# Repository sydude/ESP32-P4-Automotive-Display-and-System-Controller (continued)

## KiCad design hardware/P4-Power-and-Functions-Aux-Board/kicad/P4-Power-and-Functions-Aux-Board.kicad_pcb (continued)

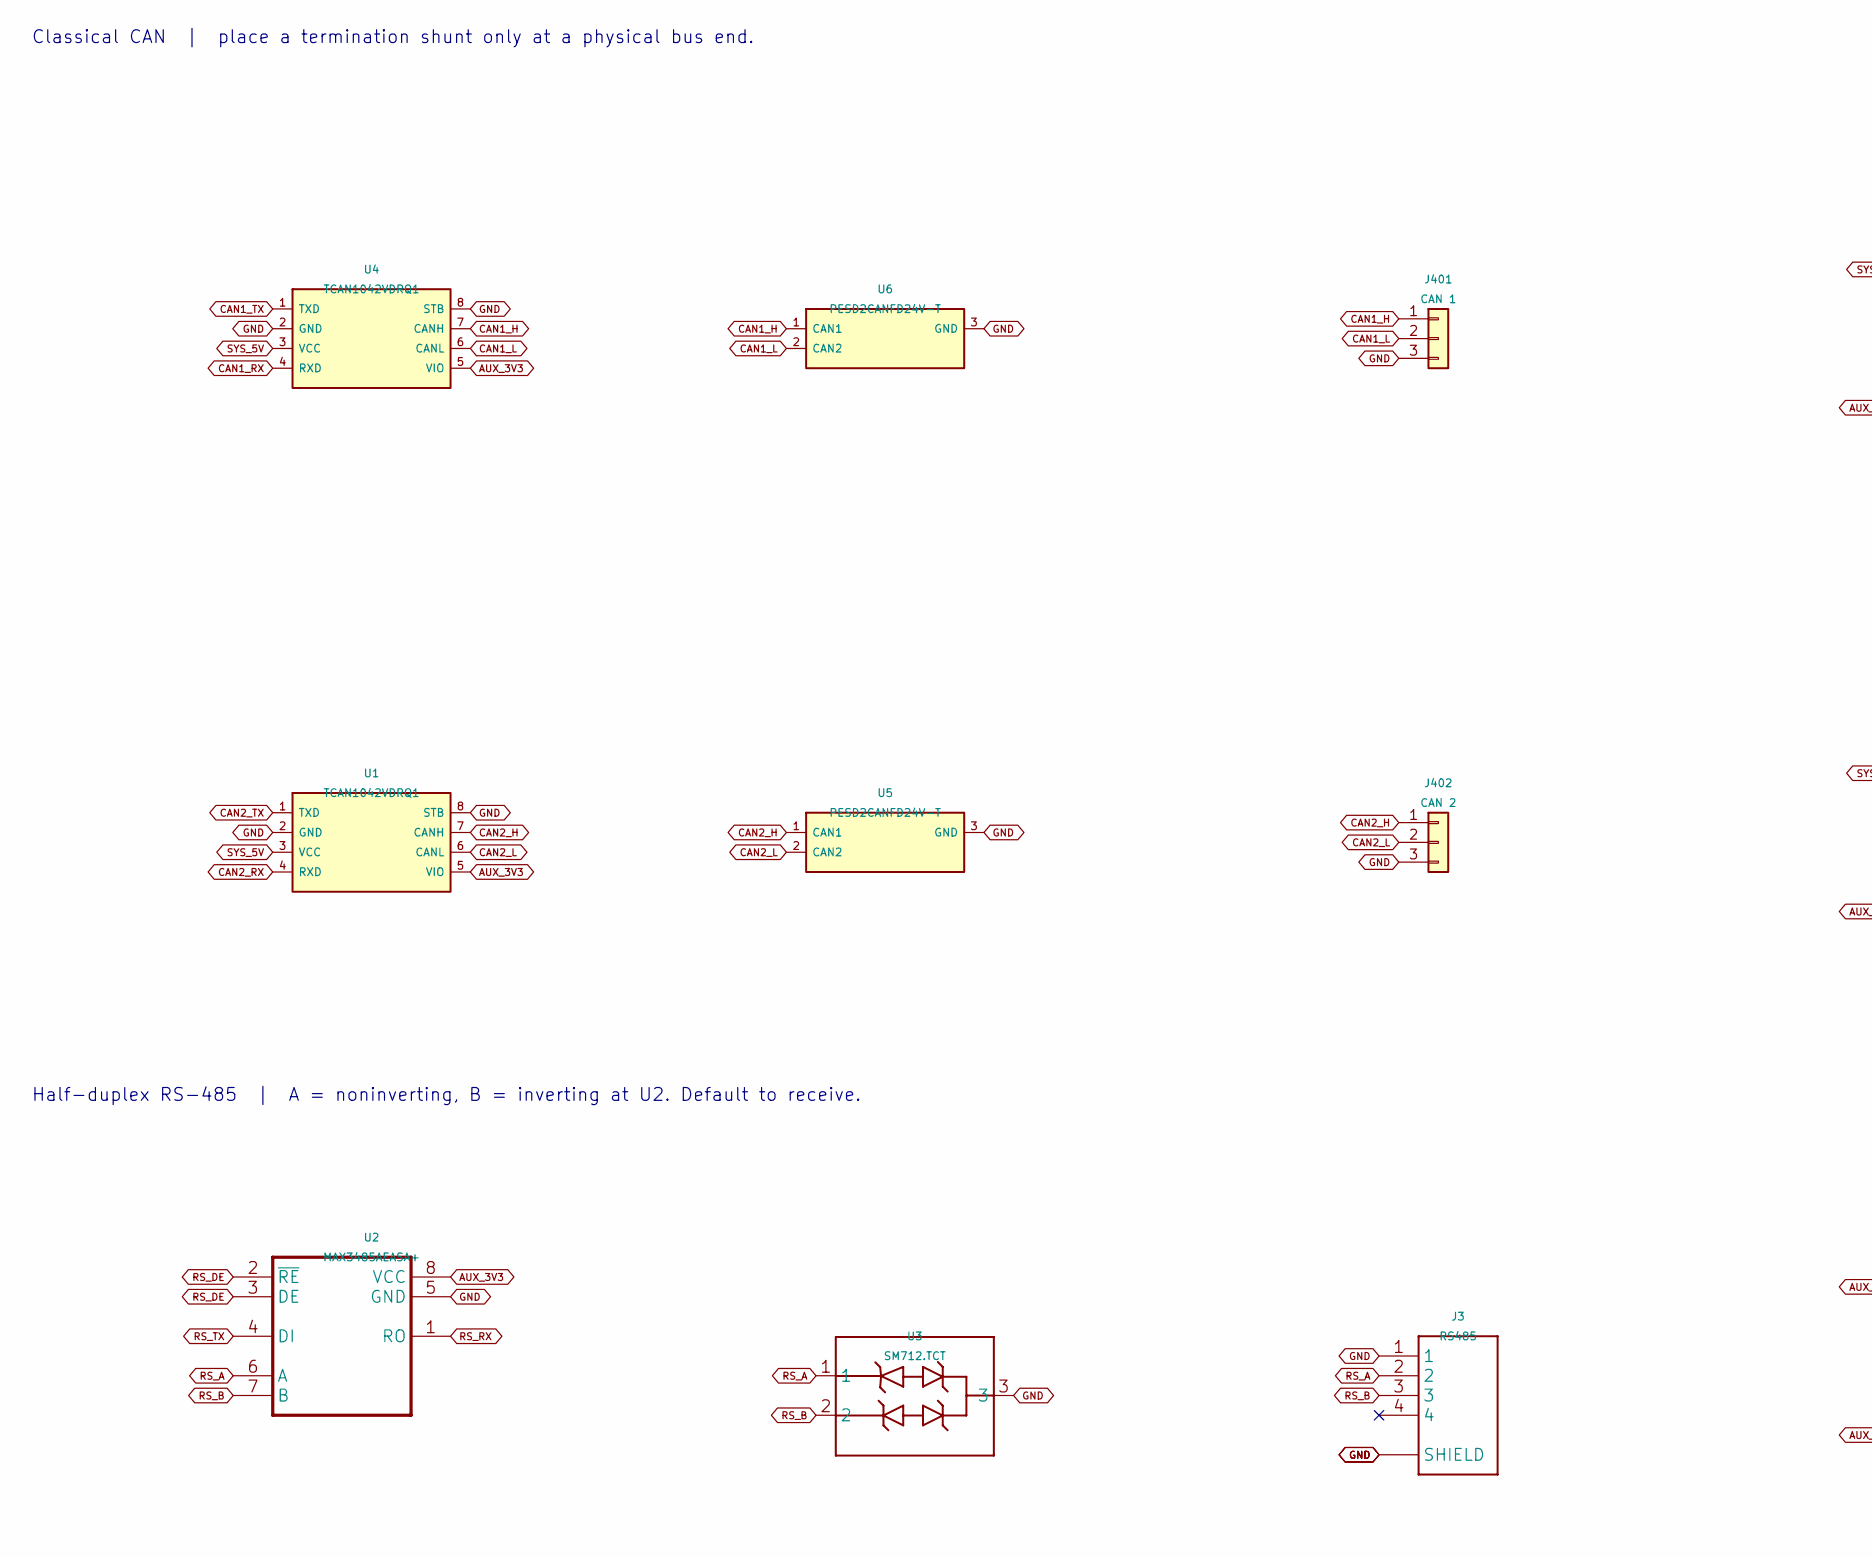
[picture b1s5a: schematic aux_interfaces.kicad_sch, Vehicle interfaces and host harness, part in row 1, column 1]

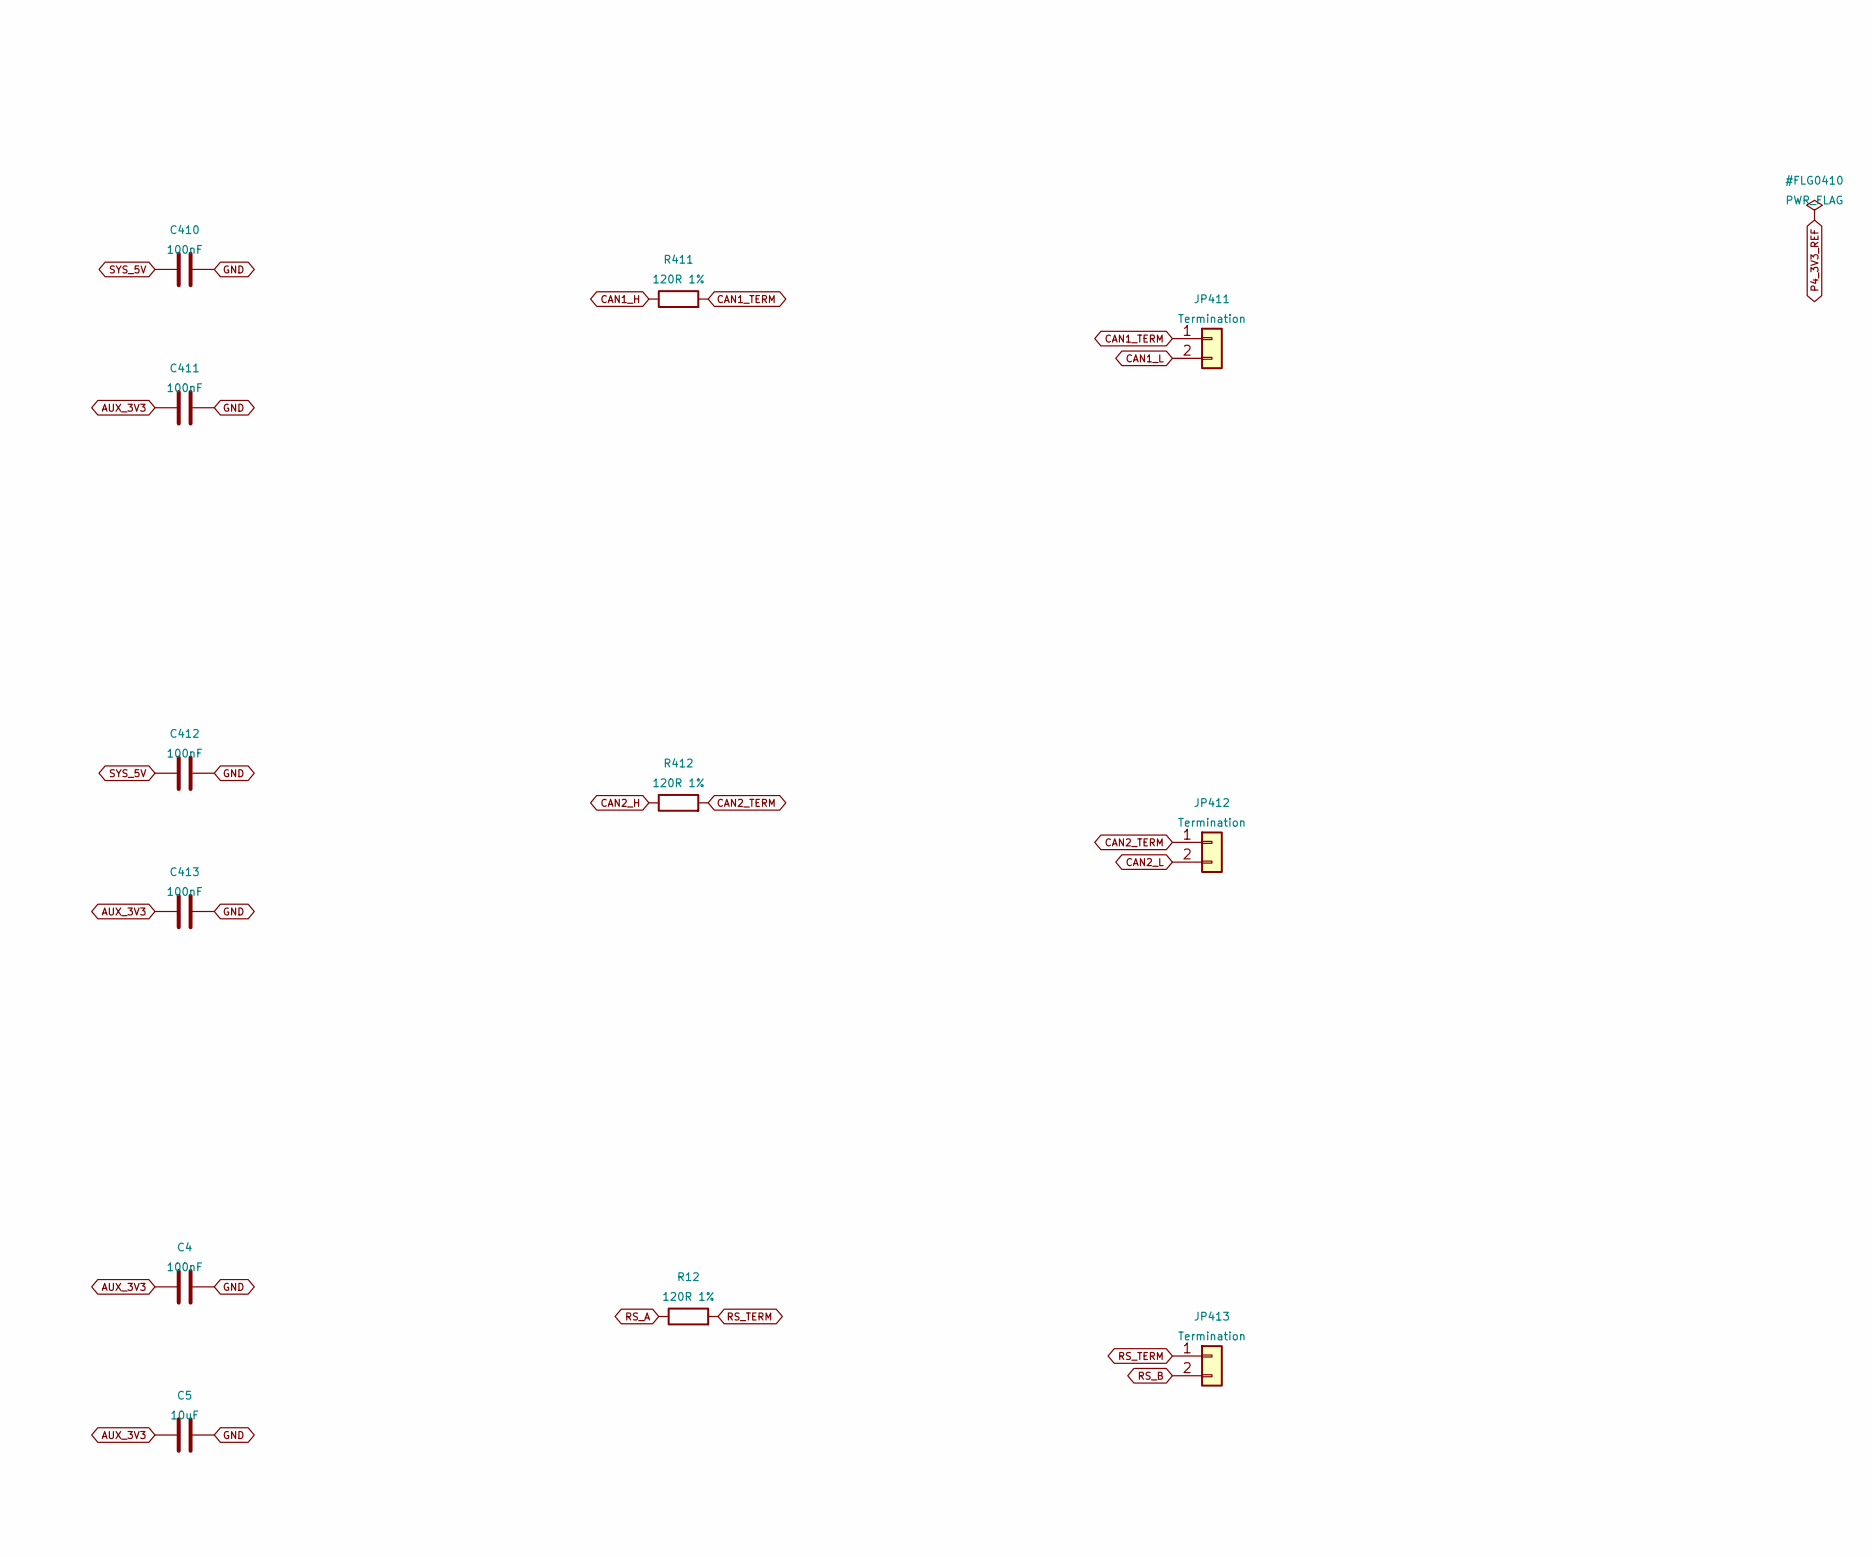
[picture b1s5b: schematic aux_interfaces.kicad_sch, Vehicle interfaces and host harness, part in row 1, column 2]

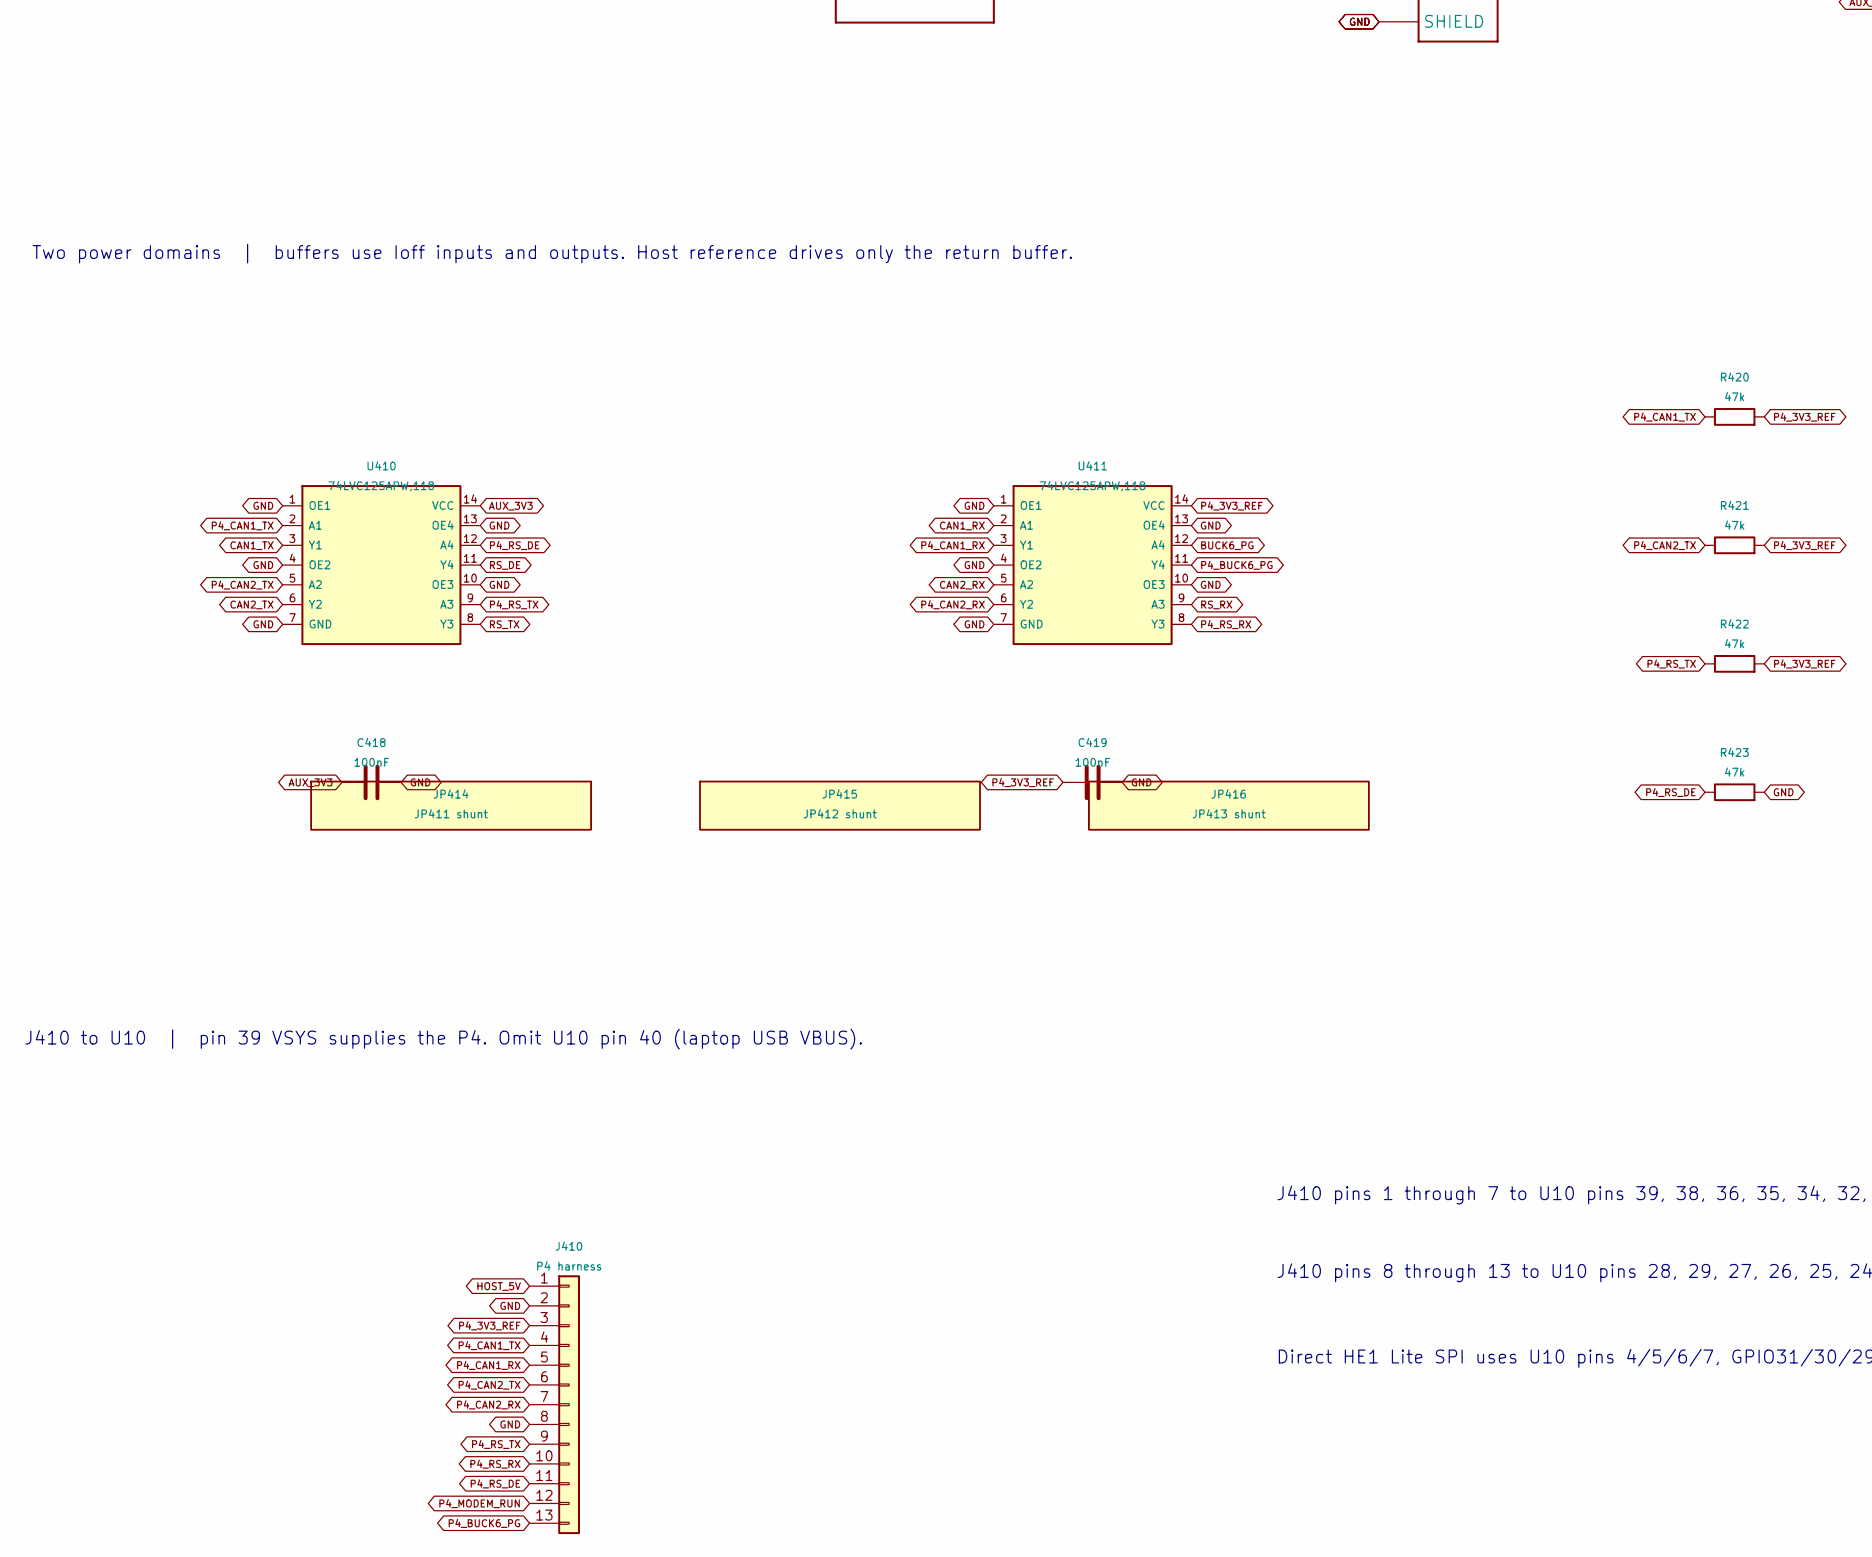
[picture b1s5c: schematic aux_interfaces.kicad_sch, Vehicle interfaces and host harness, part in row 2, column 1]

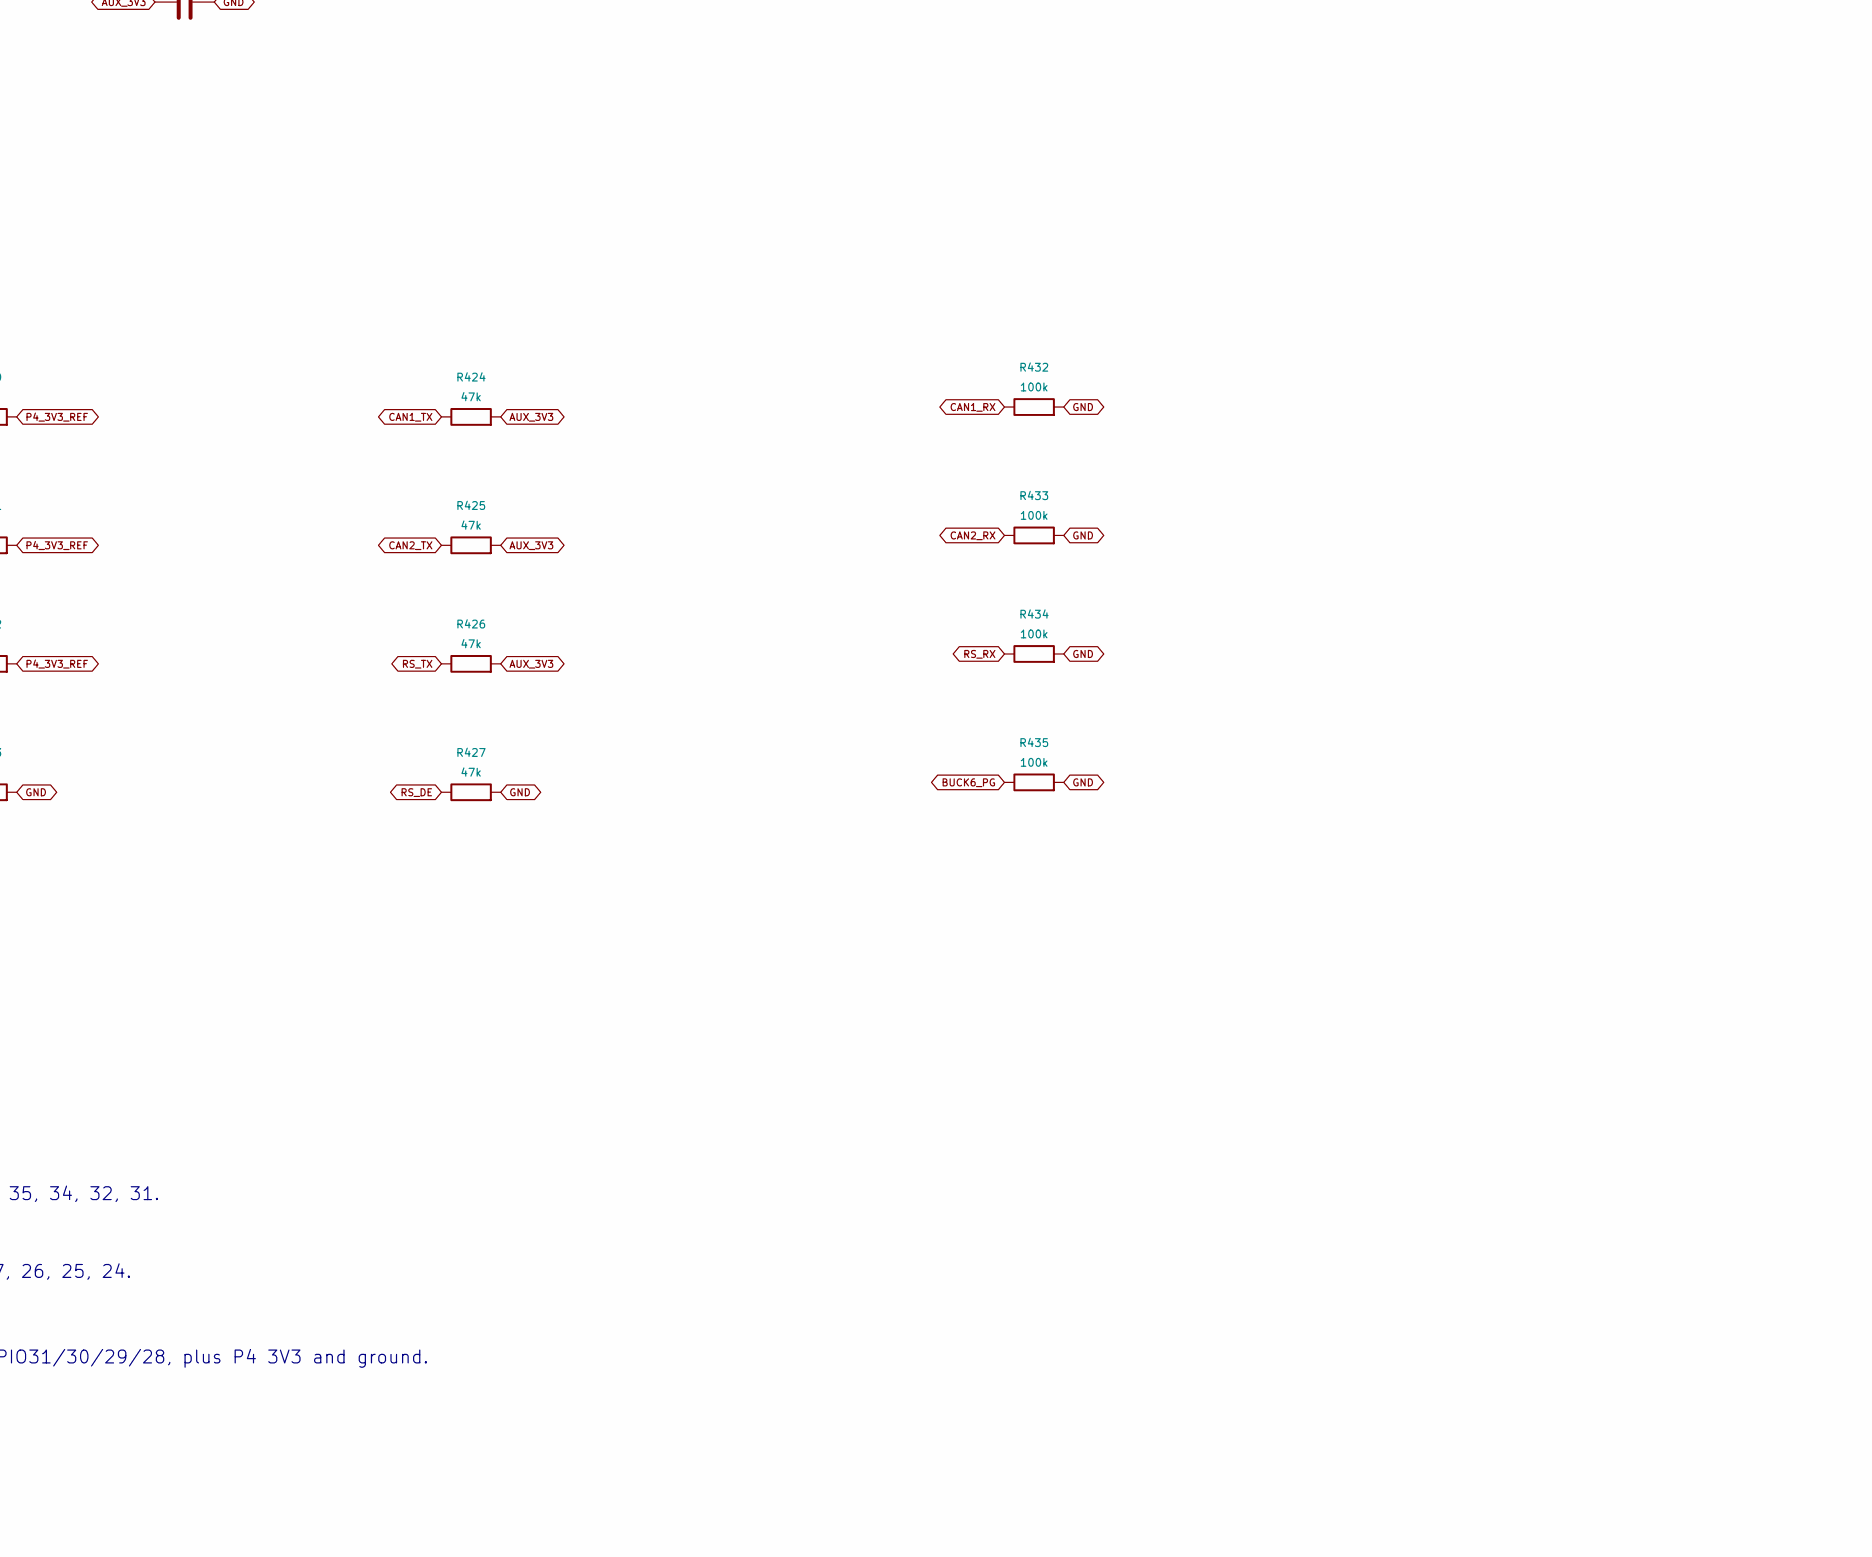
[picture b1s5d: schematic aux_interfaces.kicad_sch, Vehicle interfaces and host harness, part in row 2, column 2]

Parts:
C4, C410, C411, C412, C413, C418, C419: 100nF; C_0603_1608Metric; MPN GCM188R71C104KA37D; LCSC C184760
C5: 10uF; C_0805_2012Metric; MPN GRM21BR71A106KE51L; LCSC C86038
J3: RS485; JST_BM04B-GHS-TBT_Vertical; MPN BM04B-GHS-TBT(LF)(SN); LCSC C161692
J401: CAN 1; Molex_SL_171971-0003_1x03_P2.54mm_Vertical; MPN 171971-0003
J402: CAN 2; Molex_SL_171971-0003_1x03_P2.54mm_Vertical; MPN 171971-0003
J410: P4 harness; Molex_SL_171971-0013_1x13_P2.54mm_Vertical; MPN 171971-0013
JP411, JP412, JP413: Termination; PinHeader_1x02_P2.54mm_Vertical; MPN HX PZ2.54-1x2P ZZ; LCSC C32713268
JP414: JP411 shunt; MPN X2541-A1NIB; LCSC C2938578
JP415: JP412 shunt; MPN X2541-A1NIB; LCSC C2938578
JP416: JP413 shunt; MPN X2541-A1NIB; LCSC C2938578
R12, R411, R412: 120R 1%; R_1206_3216Metric; MPN AC1206FR-07120RL; LCSC C229293
R420, R421, R422, R423, R424, R425, R426, R427: 47k; R_0603_1608Metric; MPN AC0603FR-0747KL; LCSC C111134
R432, R433, R434, R435: 100k; R_0603_1608Metric; MPN AC0603FR-07100KL; LCSC C116674
U1, U4: TCAN1042VDRQ1; SOIC-8_3.9x4.9mm_P1.27mm; MPN TCAN1042VDRQ1; LCSC C485806
U2: MAX3485AEASA+; SOIC-8_3.9x4.9mm_P1.27mm; MPN MAX3485AEASA+T; LCSC C94609
U3: SM712.TCT; MPN SM712.TCT; LCSC C12067
U5, U6: PESD2CANFD24V-T; SOT-23; MPN PESD2CANFD24V-TR; LCSC C552486
U410, U411: 74LVC125APW,118; TSSOP-14_4.4x5mm_P0.65mm; MPN 74LVC125APW,118; LCSC C6059

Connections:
AUX_3V3: C4.1, C5.1, C411.1, C413.1, C418.1, R424.2, R425.2, R426.2, U1.5 (VIO), U2.8 (VCC), U4.5 (VIO), U410.14 (VCC); also elsewhere on the board
BUCK6_PG: R435.1, U411.12 (A4); also elsewhere on the board
CAN1_H: J401.1, R411.1, U4.7 (CANH), U6.1 (CAN1)
CAN1_L: J401.2, JP411.2, U4.6 (CANL), U6.2 (CAN2)
CAN1_RX: R432.1, U4.4 (RXD), U411.2 (A1)
CAN1_TERM: JP411.1, R411.2
CAN1_TX: R424.1, U4.1 (TXD), U410.3 (Y1)
CAN2_H: J402.1, R412.1, U1.7 (CANH), U5.1 (CAN1)
CAN2_L: J402.2, JP412.2, U1.6 (CANL), U5.2 (CAN2)
CAN2_RX: R433.1, U1.4 (RXD), U411.5 (A2)
CAN2_TERM: JP412.1, R412.2
CAN2_TX: R425.1, U1.1 (TXD), U410.6 (Y2)
GND: C4.2, C5.2, C410.2, C411.2, C412.2, C413.2, C418.2, C419.2, J3.1, J3.SH1 (SHIELD), J3.SH2 (SHIELD), J401.3, J402.3, J410.2, J410.8, R423.2, R427.2, R432.2, R433.2, R434.2, R435.2, U1.2 (GND), U1.8 (STB), U2.5 (GND), U3.3, U4.2 (GND), U4.8 (STB), U5.3 (GND), U6.3 (GND), U410.1 (OE1), U410.4 (OE2), U410.7 (GND), U410.10 (OE3), U410.13 (OE4), U411.1 (OE1), U411.4 (OE2), U411.7 (GND), U411.10 (OE3), U411.13 (OE4); also elsewhere on the board
HOST_5V: J410.1; also elsewhere on the board
P4_3V3_REF: C419.1, J410.3, R420.2, R421.2, R422.2, U411.14 (VCC)
P4_BUCK6_PG: J410.13, U411.11 (Y4)
P4_CAN1_RX: J410.5, U411.3 (Y1)
P4_CAN1_TX: J410.4, R420.1, U410.2 (A1)
P4_CAN2_RX: J410.7, U411.6 (Y2)
P4_CAN2_TX: J410.6, R421.1, U410.5 (A2)
P4_MODEM_RUN: J410.12; also elsewhere on the board
P4_RS_DE: J410.11, R423.1, U410.12 (A4)
P4_RS_RX: J410.10, U411.8 (Y3)
P4_RS_TX: J410.9, R422.1, U410.9 (A3)
RS_A: J3.2, R12.1, U2.6 (A), U3.1
RS_B: J3.3, JP413.2, U2.7 (B), U3.2
RS_DE: R427.1, U2.2 (~RE), U2.3 (DE), U410.11 (Y4)
RS_RX: R434.1, U2.1 (RO), U411.9 (A3)
RS_TERM: JP413.1, R12.2
RS_TX: R426.1, U2.4 (DI), U410.8 (Y3)
SYS_5V: C410.1, C412.1, U1.3 (VCC), U4.3 (VCC); also elsewhere on the board

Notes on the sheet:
J410 to U10 | pin 39 VSYS supplies the P4. Omit U10 pin 40 (laptop USB VBUS).
Two power domains | buffers use Ioff inputs and outputs. Host reference drives only the return buffer.
J410 pins 1 through 7 to U10 pins 39, 38, 36, 35, 34, 32, 31.
Classical CAN | place a termination shunt only at a physical bus end.
J410 pins 8 through 13 to U10 pins 28, 29, 27, 26, 25, 24.
Half-duplex RS-485 | A = noninverting, B = inverting at U2. Default to receive.
Direct HE1 Lite SPI uses U10 pins 4/5/6/7, GPIO31/30/29/28, plus P4 3V3 and ground.

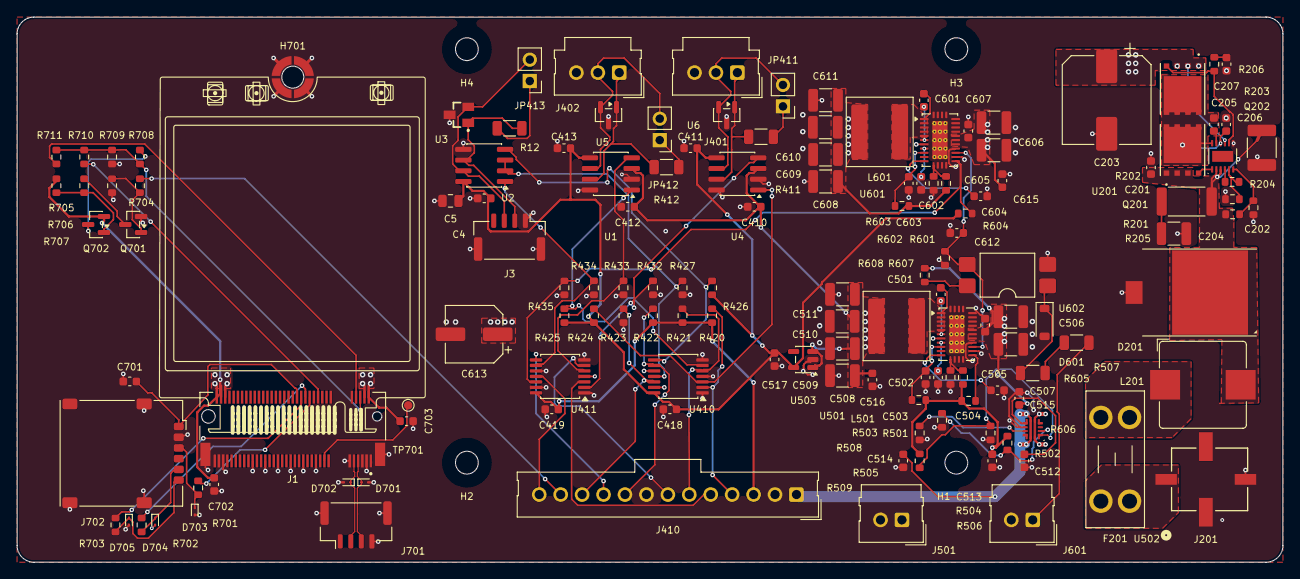
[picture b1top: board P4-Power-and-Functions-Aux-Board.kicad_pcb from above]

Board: 4 copper layers, 150.0 x 64.6 mm, 146 parts (0 on the bottom side), 84 nets.

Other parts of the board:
H1, H2, H3, H4: MountingHole_2.7mm_M2.5

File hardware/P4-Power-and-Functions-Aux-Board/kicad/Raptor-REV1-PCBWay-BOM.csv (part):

"Designators","Qty per completed unit","PCBWay purchase qty per board","Description / value","KiCad footprint","Manufacturer","Manufacturer part number","LCSC part number","Assembly","Sourcing","Availability at selection","Part link"
"C201, C205, C206","3","3","100nF 100V","Capacitor_SMD:C_0603_1608Metric","Murata","GCM188R72A104KA64D","C415406","Fit","PCBWay / LCSC","LCSC stock observed; reconfirm at quotation","https://www.lcsc.com/product-detail/C415406.html"
"C202","1","1","22uF 50V X7R","Capacitor_SMD:C_1812_4532Metric","PSA (Prosperity Dielectrics)","FS43X226K500ERG","C22388553","Fit","PCBWay / LCSC","LCSC stock observed; reconfirm at quotation","https://www.lcsc.com/product-detail/C22388553.html"
"C203","1","1","100uF 50V","Capacitor_SMD:CP_Elec_10x10","Vishay","MAL215097101E3","C2163037","Fit","PCBWay / LCSC","LCSC listed; confirm stock","https://www.lcsc.com/product-detail/C2163037.html"
"C204, C505, C506, C605, C606","5","5","10uF 50V X7R","Capacitor_SMD:C_1210_3225Metric","Murata","GRM32ER71H106KA12L","C77102","Fit","PCBWay / LCSC","LCSC stock observed; reconfirm at quotation","https://www.lcsc.com/product-detail/C77102.html"
"C207","1","1","82nF 100V X7R","Capacitor_SMD:C_0603_1608Metric","KEMET","C0603C823K1RACAUTO","C19862796","Fit","PCBWay / LCSC","LCSC last showed zero; PCBWay procurement quote required","https://www.lcsc.com/product-detail/C19862796.html"
"D201","1","1","SM8S24CA-Q","P4-Power-and-Functions-Aux-Board:Bourns_DO-218AB","Bourns","SM8S24CA-Q","C1976790","Fit","PCBWay / LCSC","LCSC listed; confirm stock","https://www.lcsc.com/product-detail/C1976790.html"
"F201","1","1","PCB-mounted MINI blade fuse holder","Fuse:Fuseholder_Blade_Mini_Keystone_3568","Keystone Electronics","3568","C5249699","Fit","PCBWay / LCSC","LCSC last showed zero; PCBWay procurement quote required","https://www.lcsc.com/product-detail/C5249699.html"
"J201","1","1","VEHICLE 12V","P4-Power-and-Functions-Aux-Board:CONN_SD-43045-007_02_MOL","Molex","43045-0218","C476811","Fit","PCBWay / LCSC","LCSC listed; confirm stock","https://www.lcsc.com/product-detail/C476811.html"
"L201","1","1","2.2uH 8A","P4-Power-and-Functions-Aux-Board:L_Bourns_SRP1038A_10.0x10.0mm","Bourns","SRP1038A-2R2M","C2042353","Fit","PCBWay / LCSC","LCSC last showed zero; PCBWay procurement quote required","https://www.lcsc.com/product-detail/C2042353.html"
"Q201, Q202","2","2","CSD19531Q5A","P4-Power-and-Functions-Aux-Board:Texas_DQJ0008A_VSONP-8","Texas Instruments","CSD19531Q5A","C2760462","Fit","PCBWay / LCSC","LCSC stock observed; reconfirm at quotation","https://www.lcsc.com/product-detail/C2760462.html"
"R201","1","1","1.0R 2W","Resistor_SMD:R_2512_6332Metric","Ever Ohms","CRH2512F1R00E04S","C2832126","Fit","PCBWay / LCSC","LCSC listed; confirm stock","https://www.lcsc.com/product-detail/C2832126.html"
"R202","1","1","56.2k 1%","Resistor_SMD:R_0603_1608Metric","Yageo","AF0603FR-0756K2L","C1882617","Fit","PCBWay / LCSC","LCSC listed; confirm stock","https://www.lcsc.com/product-detail/C1882617.html"
"R203, R504, R604, R608, R706","5","5","10k 1%","Resistor_SMD:R_0603_1608Metric","Yageo","AC0603FR-0710KL","C116677","Fit","PCBWay / LCSC","LCSC stock observed; reconfirm at quotation","https://www.lcsc.com/product-detail/C116677.html"
"R204, R505, R506, R507, R432, R433, R434, R435, R705, R710, R711","11","11","100k 1%","Resistor_SMD:R_0603_1608Metric","Yageo","AC0603FR-07100KL","C116674","Fit","PCBWay / LCSC","LCSC stock observed; reconfirm at quotation","https://www.lcsc.com/product-detail/C116674.html"
"R205","1","1","6.49k 1%","Resistor_SMD:R_0603_1608Metric","Yageo","RC0603FR-076K49L","C163421","Fit","PCBWay / LCSC","LCSC stock observed; reconfirm at quotation","https://www.lcsc.com/product-detail/C163421.html"
"R206","1","1","100R 1%","Resistor_SMD:R_0603_1608Metric","Panasonic","ERJ-3EKF1000V","C193336","Fit","PCBWay / LCSC","LCSC stock observed; reconfirm at quotation","https://www.lcsc.com/product-detail/C193336.html"
"U201","1","1","LM74800QDRRRQ1","P4-Power-and-Functions-Aux-Board:Texas_DRR0012E_WSON-12_3x3mm_P0.5mm_EP1.3x2.5mm","Texas Instruments","LM74800QDRRRQ1","C3215600","Fit","PCBWay / LCSC","LCSC stock observed; reconfirm at quotation","https://www.lcsc.com/product-detail/C3215600.html"
"C501, C601","2","2","470nF","Capacitor_SMD:C_0603_1608Metric","Murata","GRM188R71E474KA12D","C77052","Fit","PCBWay / LCSC","LCSC stock observed; reconfirm at quotation","https://www.lcsc.com/product-detail/C77052.html"
"C502, C602","2","2","2.2uF 10V","Capacitor_SMD:C_0603_1608Metric","Murata","GRM188R71A225KE15D","C86018","Fit","PCBWay / LCSC","LCSC stock observed; reconfirm at quotation","https://www.lcsc.com/product-detail/C86018.html"
"C503, C603, C513, C514, C516, C702","6","6","1uF 16V X7R","Capacitor_SMD:C_0603_1608Metric","Murata","GCM188R71C105KA64D","C161212","Fit","PCBWay / LCSC","LCSC stock observed; reconfirm at quotation","https://www.lcsc.com/product-detail/C161212.html"
"C504, C604","2","2","22nF","Capacitor_SMD:C_0603_1608Metric","Murata","GRM188R71H223KA01D","C77056","Fit","PCBWay / LCSC","LCSC stock observed; reconfirm at quotation","https://www.lcsc.com/product-detail/C77056.html"
"C507, C515, C607, C615","4","4","47nF 100V","Capacitor_SMD:C_0603_1608Metric","KEMET","C0603C473K1RAC7867","C3881354","Fit","PCBWay / LCSC","LCSC listed; confirm stock","https://www.lcsc.com/product-detail/C3881354.html"
"C508, C509, C510, C511, C608, C609, C610, C611","8","8","22uF 10V","Capacitor_SMD:C_1210_3225Metric","Murata","GCM32ER71A226KE12L","C913632","Fit","PCBWay / LCSC","LCSC stock observed; reconfirm at quotation","https://www.lcsc.com/product-detail/C913632.html"
"C512, C612","2","2","10nF","Capacitor_SMD:C_0603_1608Metric","Murata","GCM188R71H103KA37D","C85863","Fit","PCBWay / LCSC","LCSC listed; confirm stock","https://www.lcsc.com/product-detail/C85863.html"
"C517","1","1","4.7uF","Capacitor_SMD:C_0603_1608Metric","Murata","GRM188R61A475KE15D","C71633","Fit","PCBWay / LCSC","LCSC stock observed; reconfirm at quotation","https://www.lcsc.com/product-detail/C71633.html"
"L501, L601","2","2","10uH","Inductor_SMD:L_Coilcraft_XAL7070-XXX","Coilcraft","XAL7070-103MEC","C55598417","Fit","PCBWay / LCSC","LCSC listed; confirm stock","https://www.lcsc.com/product-detail/C55598417.html"
"R501","1","1","100k 0.1%","Resistor_SMD:R_0603_1608Metric","Yageo","RT0603BRD07100KL","C122538","Fit","PCBWay / LCSC","LCSC stock observed; reconfirm at quotation","https://www.lcsc.com/product-detail/C122538.html"
"R502, R602","2","2","24.9k 0.1%","Resistor_SMD:R_0603_1608Metric","Ever Ohms","TR0603B24K9P0525Z","C149931","Fit","PCBWay / LCSC","LCSC stock observed; reconfirm at quotation","https://www.lcsc.com/product-detail/C149931.html"
"R503, R603","2","2","4.7R","Resistor_SMD:R_0603_1608Metric","Yageo","AC0603FR-074R7L","C144651","Fit","PCBWay / LCSC","LCSC stock observed; reconfirm at quotation","https://www.lcsc.com/product-detail/C144651.html"
"R508","1","1","26.7k","Resistor_SMD:R_0603_1608Metric","Yageo","RC0603FR-0726K7L","C137756","Fit","PCBWay / LCSC","LCSC stock observed; reconfirm at quotation","https://www.lcsc.com/product-detail/C137756.html"
"R509","1","1","1.05k","Resistor_SMD:R_0603_1608Metric","Panasonic","ERJ-3EKF1051V","C402872","Fit","PCBWay / LCSC","LCSC stock observed; reconfirm at quotation","https://www.lcsc.com/product-detail/C402872.html"
"U501, U601","2","2","LM76003QRNPRQ1","P4-Power-and-Functions-Aux-Board:Texas_RNP0030B_WQFN-30-1EP_4x6mm_P0.5mm_EP1.8x4.5mm_ThermalVias","Texas Instruments","LM76003QRNPRQ1","C2073028","Fit","PCBWay / LCSC","LCSC last showed zero; PCBWay procurement quote required","https://www.lcsc.com/product-detail/C2073028.html"
"U502","1","1","TPS259470ARPWR","P4-Power-and-Functions-Aux-Board:Texas_RPW0010A_VQFN-HR-10_2x2mm","Texas Instruments","TPS259470ARPWR","C3662799","Fit","PCBWay / LCSC","LCSC stock observed; reconfirm at quotation","https://www.lcsc.com/product-detail/C3662799.html"
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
